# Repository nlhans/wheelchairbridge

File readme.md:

#### wheelchair bridge 

Simple circuit using I2C digipot to emulate two-axis joystick following
(reasonable common) DB9 pinout.

Typically, a joystick for a wheelchair generates a +/- 1V around a 6V (mid 12V) center voltage. 

Note that the situation when the pico is powered off (and signals go to zero)

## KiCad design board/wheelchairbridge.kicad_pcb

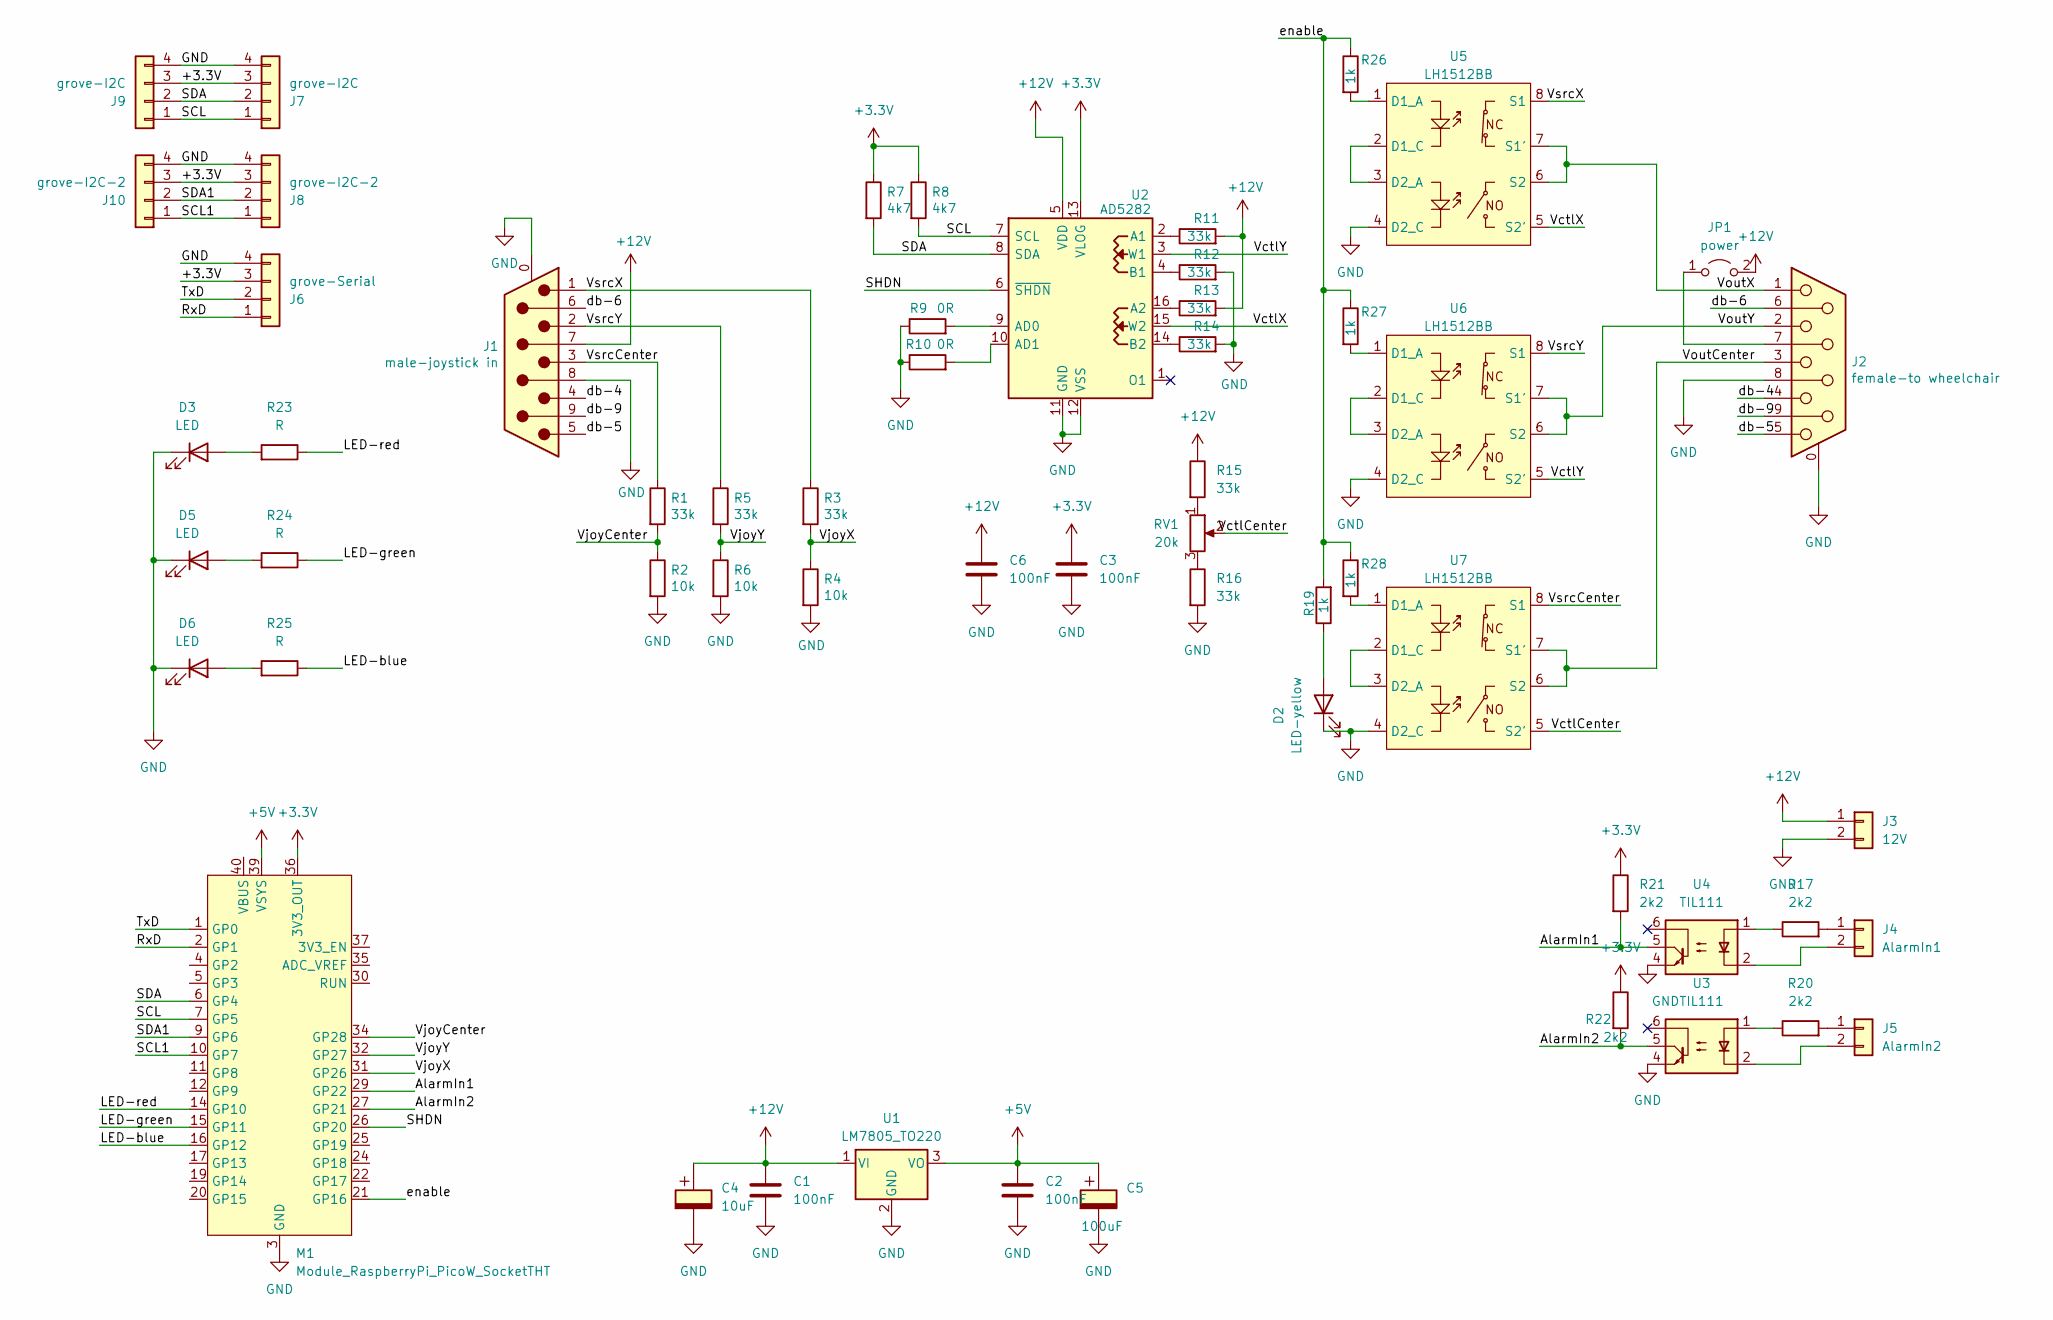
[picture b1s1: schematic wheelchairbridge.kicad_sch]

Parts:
C1, C2, C3, C6: 100nF; C_1206_3216Metric
C4: 10uF; CP_Elec_D6.3mm_H6.1mm
C5: 100uF; CP_Elec_D6.3mm_H6.1mm
D2: LED-yellow; LED_1206_3216Metric_Pad1.42x1.75mm_HandSolder
D3, D5, D6: LED; LED_1206_3216Metric_Pad1.42x1.75mm_HandSolder
J1: male-joystick in; DSUB-9_Pins_Horizontal_P2.77x2.84mm_EdgePinOffset4.94mm_Hou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
J2: female-to wheelchair; DSUB-9_Socket_Horizontal_P2.77x2.84mm_EdgePinOffset4.94mm_H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
J3: 12V; TerminalBlock_bornier-2_P5.08mm
J4: AlarmIn1; TerminalBlock_bornier-2_P5.08mm
J5: AlarmIn2; TerminalBlock_bornier-2_P5.08mm
J6: grove-Serial; NS-Tech_Grove_1x04_P2mm_Vertical
J7, J9: grove-I2C; NS-Tech_Grove_1x04_P2mm_Vertical
J8, J10: grove-I2C-2; NS-Tech_Grove_1x04_P2mm_Vertical
JP1: power; PinHeader_1x02_P2.54mm_Vertical
M1: Module_RaspberryPi_PicoW_SocketTHT; RaspberryPi_PicoW_SocketTHT
R1, R3, R5, R11, R12, R13, R14, R15, R16: 33k; R_0805_2012Metric
R2, R4, R6: 10k; R_0805_2012Metric
R7, R8: 4k7; R_0805_2012Metric
R9, R10: 0R; R_0805_2012Metric
R17, R20, R21, R22: 2k2; R_0805_2012Metric
R19, R26, R27, R28: 1k; R_0805_2012Metric
R23, R24, R25: R; R_0805_2012Metric
RV1: 20k; Potentiometer_Bourns_3314R-1_Vertical_Hole
U1: LM7805_TO220; TO-220-3_Vertical
U2: AD5282; TSSOP-16_4.4x5mm_P0.65mm
U3, U4: TIL111; DIP-6_W7.62mm
U5, U6, U7: LH1512BB; DIP-8_W7.62mm_Socket_LongPads

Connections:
+3.3V: C3.1, J6.3, J7.3, J8.3, J9.3, J10.3, M1.36 (3V3_OUT), R7.1, R8.1, R21.1, R22.1, U2.13 (VLOG)
+5V: C2.1, C5.1, M1.39 (VSYS), U1.3 (VO)
+12V: C1.1, C4.1, C6.1, J1.7, J3.1, JP1.2 (B), R11.2, R13.2, R15.1, U1.1 (VI), U2.5 (VDD)
/AlarmIn1: M1.29 (GP22), R21.2, U4.5
/AlarmIn2: M1.27 (GP21), R22.2, U3.5
/LED-blue: M1.16 (GP12), R25.1
/LED-green: M1.15 (GP11), R24.1
/LED-red: M1.14 (GP10), R23.1
/RxD: J6.1, M1.2 (GP1)
/SCL: J7.1, J9.1, M1.7 (GP5), R8.2, U2.7 (SCL)
/SCL1: J8.1, J10.1, M1.10 (GP7)
/SDA: J7.2, J9.2, M1.6 (GP4), R7.2, U2.8 (SDA)
/SDA1: J8.2, J10.2, M1.9 (GP6)
/SHDN: M1.26 (GP20), U2.6 (~SHDN)
/TxD: J6.2, M1.1 (GP0)
/VctlCenter: RV1.2, U7.5 (S2')
/VctlX: U2.15 (W2), U5.5 (S2')
/VctlY: U2.3 (W1), U6.5 (S2')
/VjoyCenter: M1.34 (GP28), R1.2, R2.1
/VjoyX: M1.31 (GP26), R3.2, R4.1
/VjoyY: M1.32 (GP27), R5.2, R6.1
/VoutCenter: J2.3, U7.6 (S2), U7.7 (S1')
/VoutX: J2.1, U5.6 (S2), U5.7 (S1')
/VoutY: J2.2, U6.6 (S2), U6.7 (S1')
/VsrcCenter: J1.3, R1.1, U7.8 (S1)
/VsrcX: J1.1, R3.1, U5.8 (S1)
/VsrcY: J1.2, R5.1, U6.8 (S1)
/db-4: J1.4, J2.4
/db-5: J1.5, J2.5
/db-6: J1.6, J2.6
/db-9: J1.9, J2.9
/enable: M1.21 (GP16), R19.2, R26.1, R27.1, R28.1
GND: C1.2, C2.2, C3.2, C4.2, C5.2, C6.2, D2.1 (K), D3.1 (K), D5.1 (K), D6.1 (K), J1.0 (PAD), J1.8, J2.0 (PAD), J2.8, J3.2, J6.4, J7.4, J8.4, J9.4, J10.4, M1.3 (GND), M1.8 (GND), M1.13 (GND), M1.18 (GND), M1.23 (GND), M1.28 (GND), M1.33 (GND), M1.38 (GND), R2.2, R4.2, R6.2, R9.1, R10.1, R12.2, R14.2, R16.2, U1.2 (GND), U2.11 (GND), U2.12 (VSS), U3.4, U4.4, U5.4 (D2_C), U6.4 (D2_C), U7.4 (D2_C)
unnamed: D2.2 (A), R19.1
unnamed: D3.2 (A), R23.2
unnamed: D5.2 (A), R24.2
unnamed: D6.2 (A), R25.2
unnamed: J4.1, R17.2
unnamed: J4.2, U4.2
unnamed: J5.1, R20.2
unnamed: J5.2, U3.2
unnamed: J2.7, JP1.1 (A)
unnamed: R15.2, RV1.1
unnamed: R16.1, RV1.3
unnamed: R17.1, U4.1
unnamed: R20.1, U3.1
unnamed: R11.1, U2.2 (A1)
unnamed: R13.1, U2.16 (A2)
unnamed: R9.2, U2.9 (AD0)
unnamed: R10.2, U2.10 (AD1)
unnamed: R12.1, U2.4 (B1)
unnamed: R14.1, U2.14 (B2)
unnamed: R26.2, U5.1 (D1_A)
unnamed: U5.2 (D1_C), U5.3 (D2_A)
unnamed: R27.2, U6.1 (D1_A)
unnamed: U6.2 (D1_C), U6.3 (D2_A)
unnamed: R28.2, U7.1 (D1_A)
unnamed: U7.2 (D1_C), U7.3 (D2_A)

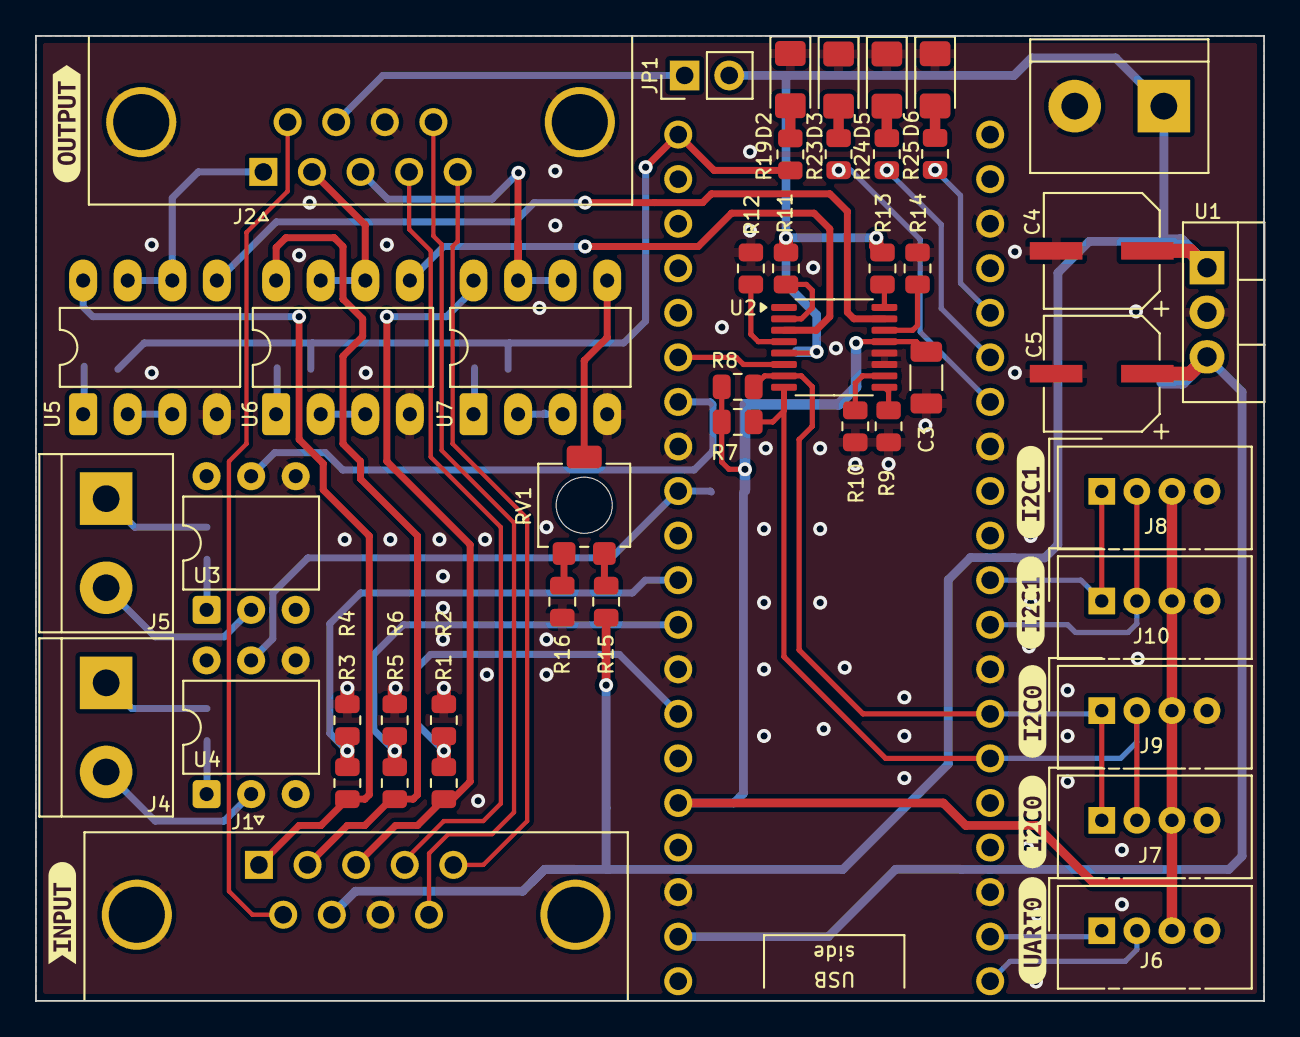
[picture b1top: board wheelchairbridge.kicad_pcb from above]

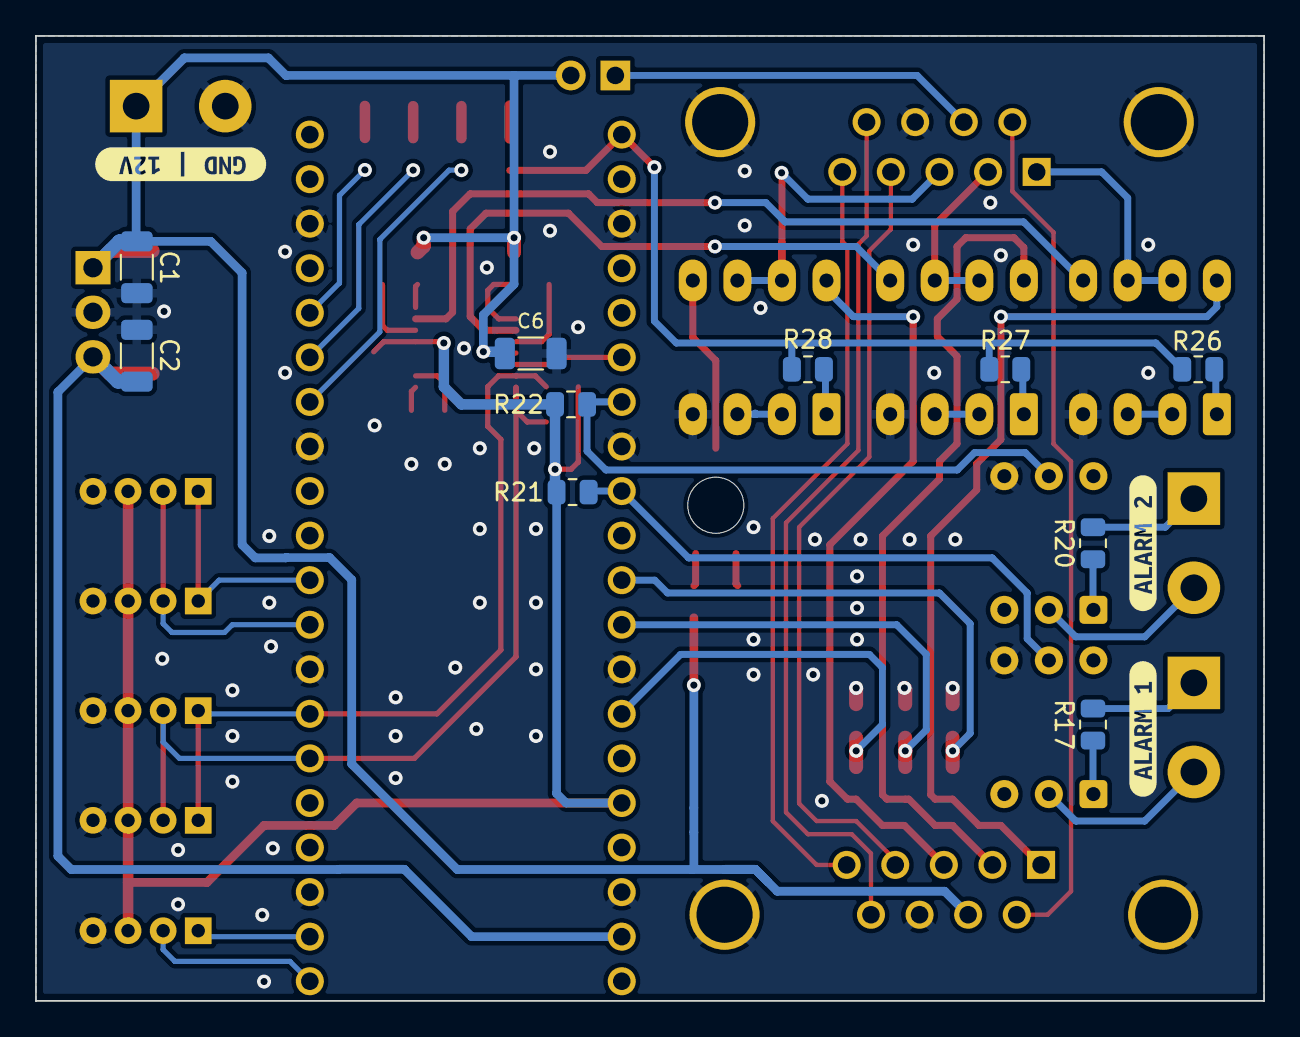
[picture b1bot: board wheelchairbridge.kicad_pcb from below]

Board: 2 copper layers, 70.0 x 55.0 mm, 67 parts (13 on the bottom side), 58 nets.

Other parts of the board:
kibuzzard-681B4A1A, kibuzzard-681B4A1A#2: G***; kibuzzard-681B4A1A
kibuzzard-681B4A2D, kibuzzard-681B4A2D#2: G***; kibuzzard-681B4A2D
kibuzzard-681B4A44: G***; kibuzzard-681B4A44
kibuzzard-681B47BC: G***; kibuzzard-681B47BC
kibuzzard-681B47CA: G***; kibuzzard-681B47CA
kibuzzard-681B4932: G***; kibuzzard-681B4932
kibuzzard-681C614D: G***; kibuzzard-681C614D
kibuzzard-681C6150: G***; kibuzzard-681C6150

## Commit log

2025-04-30 added readme
2025-05-07 Added Solid State relays for low-power signal switching. Switch from edge to regular DB9 connectors Refactored schematic PCB layout
2025-05-08 Alarm labels were wrong Added 100nF cap on 12V for digipot
2025-08-04 Interactive BOM for assembly Test Arduino Sketch with R-DAC and relays.
